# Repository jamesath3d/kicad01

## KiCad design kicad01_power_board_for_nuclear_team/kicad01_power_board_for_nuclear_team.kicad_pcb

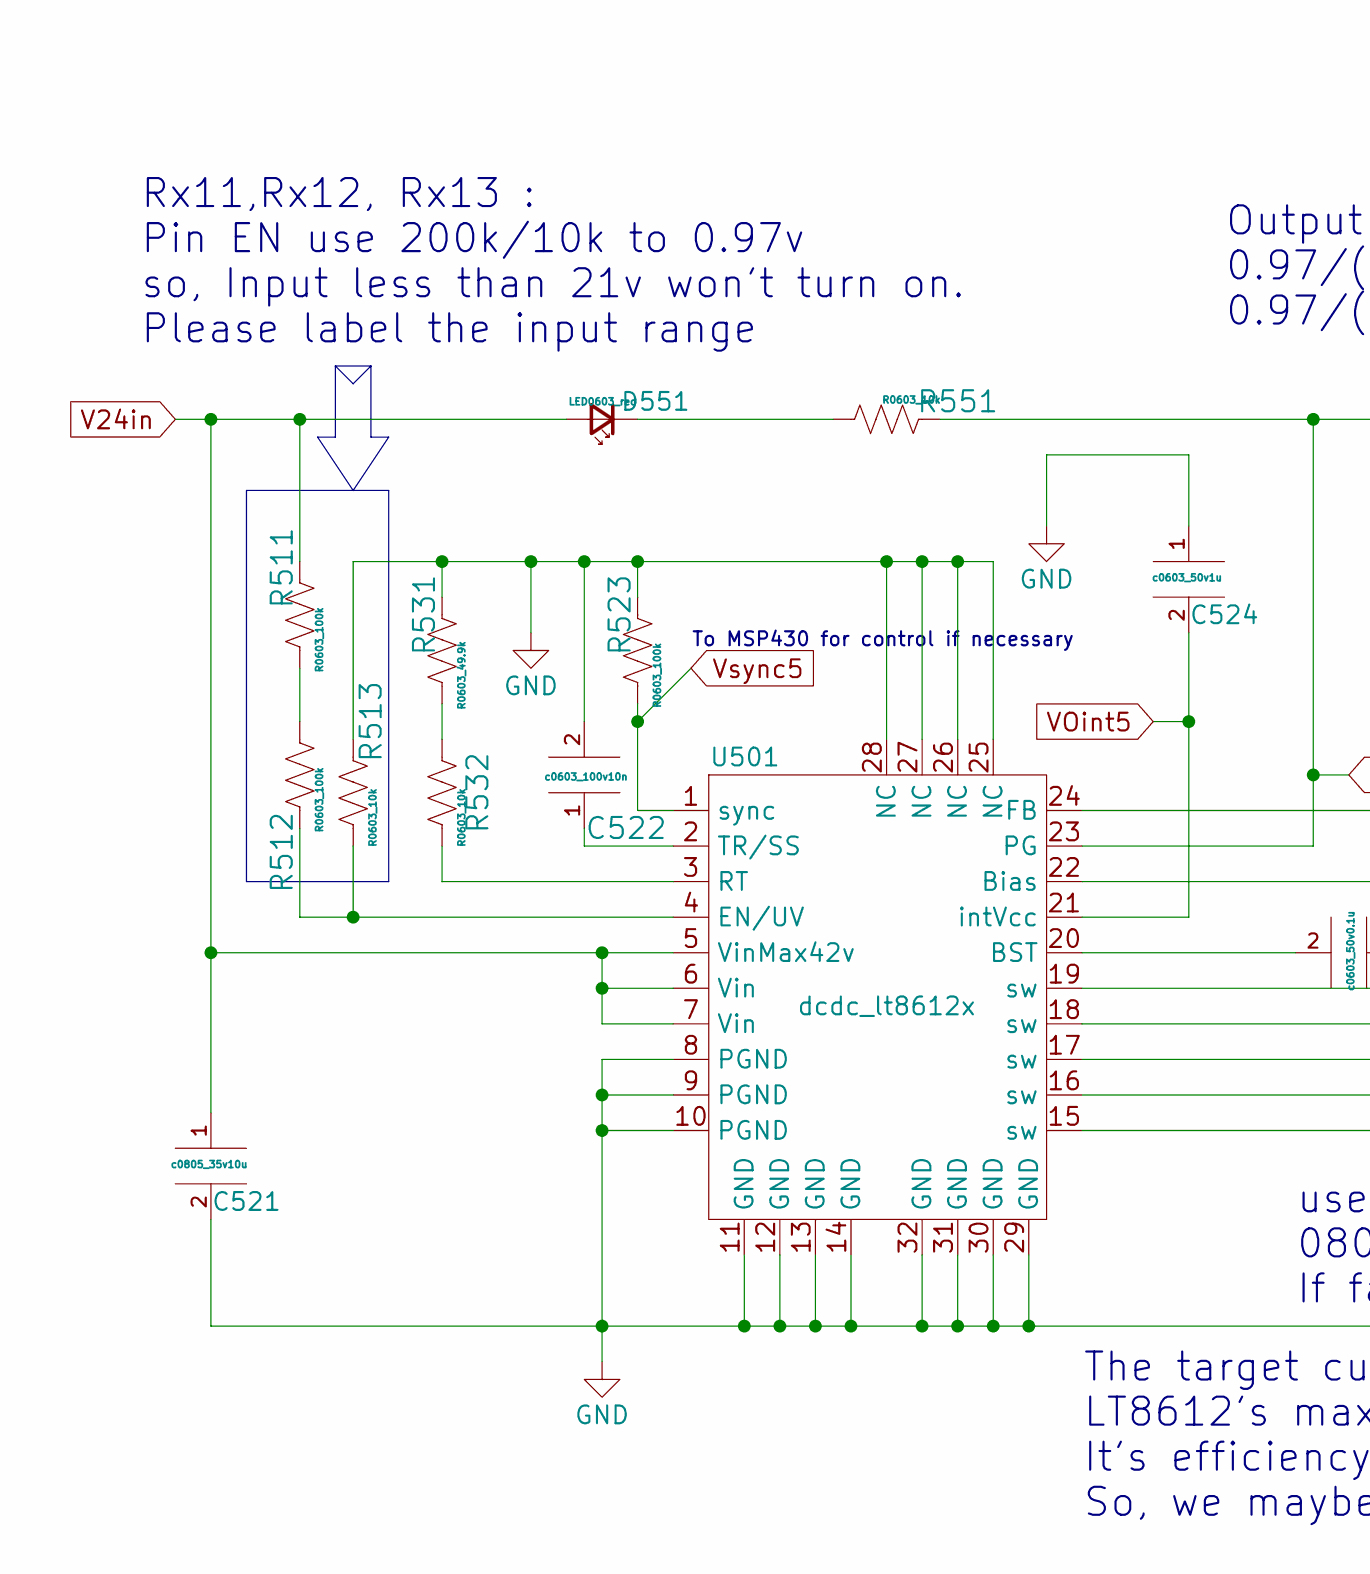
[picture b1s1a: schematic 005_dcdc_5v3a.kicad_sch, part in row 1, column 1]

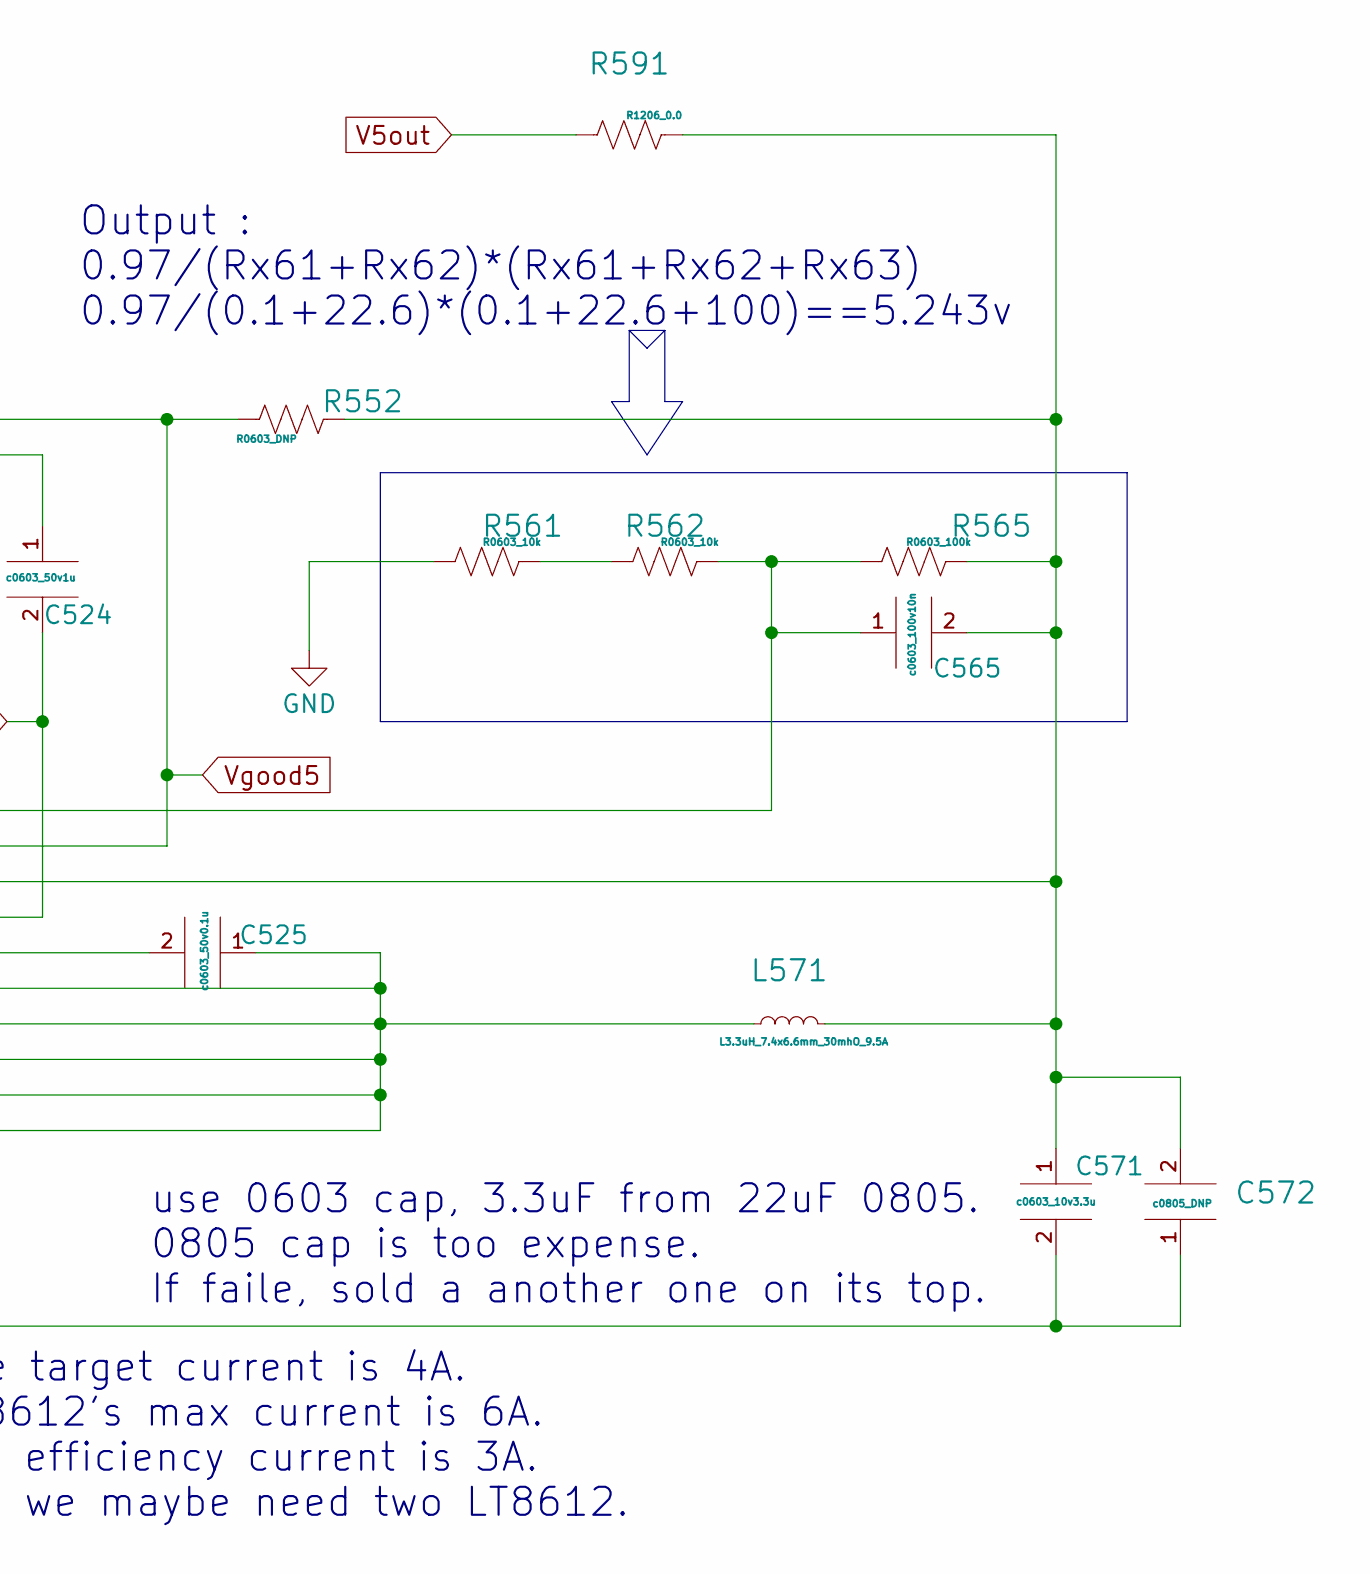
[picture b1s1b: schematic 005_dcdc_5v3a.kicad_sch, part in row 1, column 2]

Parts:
C521: c0805_35v10u; C0805mix0603; PartNum C2012X5R1V106M085AC
C522, C565: c0603_100v10n; C0603; PartNum C1608X7R2A103M080AA
C524: c0603_50v1u; C0603; PartNum C1608X5R1H105K080AB
C525: c0603_50v0.1u; C0603; PartNum CGA3E2X7R1H104M080AA
C571: c0603_10v3.3u; C0603; PartNum C1608X7S1A335K080AC
C572: c0805_DNP; C0805mix0603; PartNum c0805_DNP
D551: LED0603_red; LED0603; PartNum LTST-C190KRKT
L571: L3.3uH_7.4x6.6mm_30mhO_9.5A; L7.1x6.6mm; PartNum ECS-MPIL0630-3R3MC
R511, R512, R523, R565: R0603_100k; C0603; PartNum ERA-3AED104V
R513, R532, R551, R561, R562: R0603_10k; C0603; PartNum ERJ-PA3F1002V
R531: R0603_49.9k; C0603; PartNum ERA-3AED4992V
R552: R0603_DNP; C0603; PartNum R0603_DNP
R591: R1206_0.0; R1206mix0603; PartNum RC1206FR-070RL
U501: dcdc_lt8612x; QFN-28-1EP_3x6mm_P0.5mm_EP1.7x4.75mmX; PartNum 505-LT8612EUDE#PBF-ND

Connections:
GND: C521.2, C522.2, C524.1, C571.2, C572.1, R513.2, R523.2, R531.2, R561.2, U501.8 (PGND), U501.9 (PGND), U501.10 (PGND), U501.11 (GND), U501.12 (GND), U501.13 (GND), U501.14 (GND), U501.25 (NC), U501.26 (NC), U501.27 (NC), U501.28 (NC), U501.29 (GND), U501.30 (GND), U501.31 (GND), U501.32 (GND); also elsewhere on the board
unnamed: C522.1, U501.2 (TR/SS)
unnamed: C525.1, L571.1, U501.15 (sw), U501.16 (sw), U501.17 (sw), U501.18 (sw), U501.19 (sw)
unnamed: C525.2, U501.20 (BST)
unnamed: C565.1, R562.1, R565.2, U501.24 (FB)
unnamed: C565.2, C571.1, C572.2, L571.2, R552.2, R565.1, R591.1, U501.22 (Bias)
unnamed: D551.1 (K), R551.2
unnamed: R511.1, R512.2
unnamed: R512.1, R513.1, U501.4 (EN/UV)
unnamed: R531.1, R532.2
unnamed: R532.1, U501.3 (RT)
unnamed: R561.1, R562.2
V5out: R591.2; also elsewhere on the board
V24in: C521.1, D551.2 (A), R511.2, U501.5 (VinMax42v), U501.6 (Vin), U501.7 (Vin); also elsewhere on the board
VOint5: C524.2, U501.21 (intVcc)
Vgood5: R551.1, R552.1, U501.23 (PG)
Vsync5: R523.1, U501.1 (sync)

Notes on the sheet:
use 0603 cap, 3.3uF from 22uF 0805. 0805 cap is too expense. If faile, sold a another one on its top.
To MSP430 for control if necessary
The target current is 4A. LT8612's max current is 6A. It's efficiency current is 3A. So, we maybe need two LT8612.
Output : 0.97/(Rx61+Rx62)*(Rx61+Rx62+Rx63) 0.97/(0.1+22.6)*(0.1+22.6+100)==5.243v
Rx11,Rx12, Rx13 : Pin EN use 200k/10k to 0.97v so, Input less than 21v won't turn on. Please label the input range

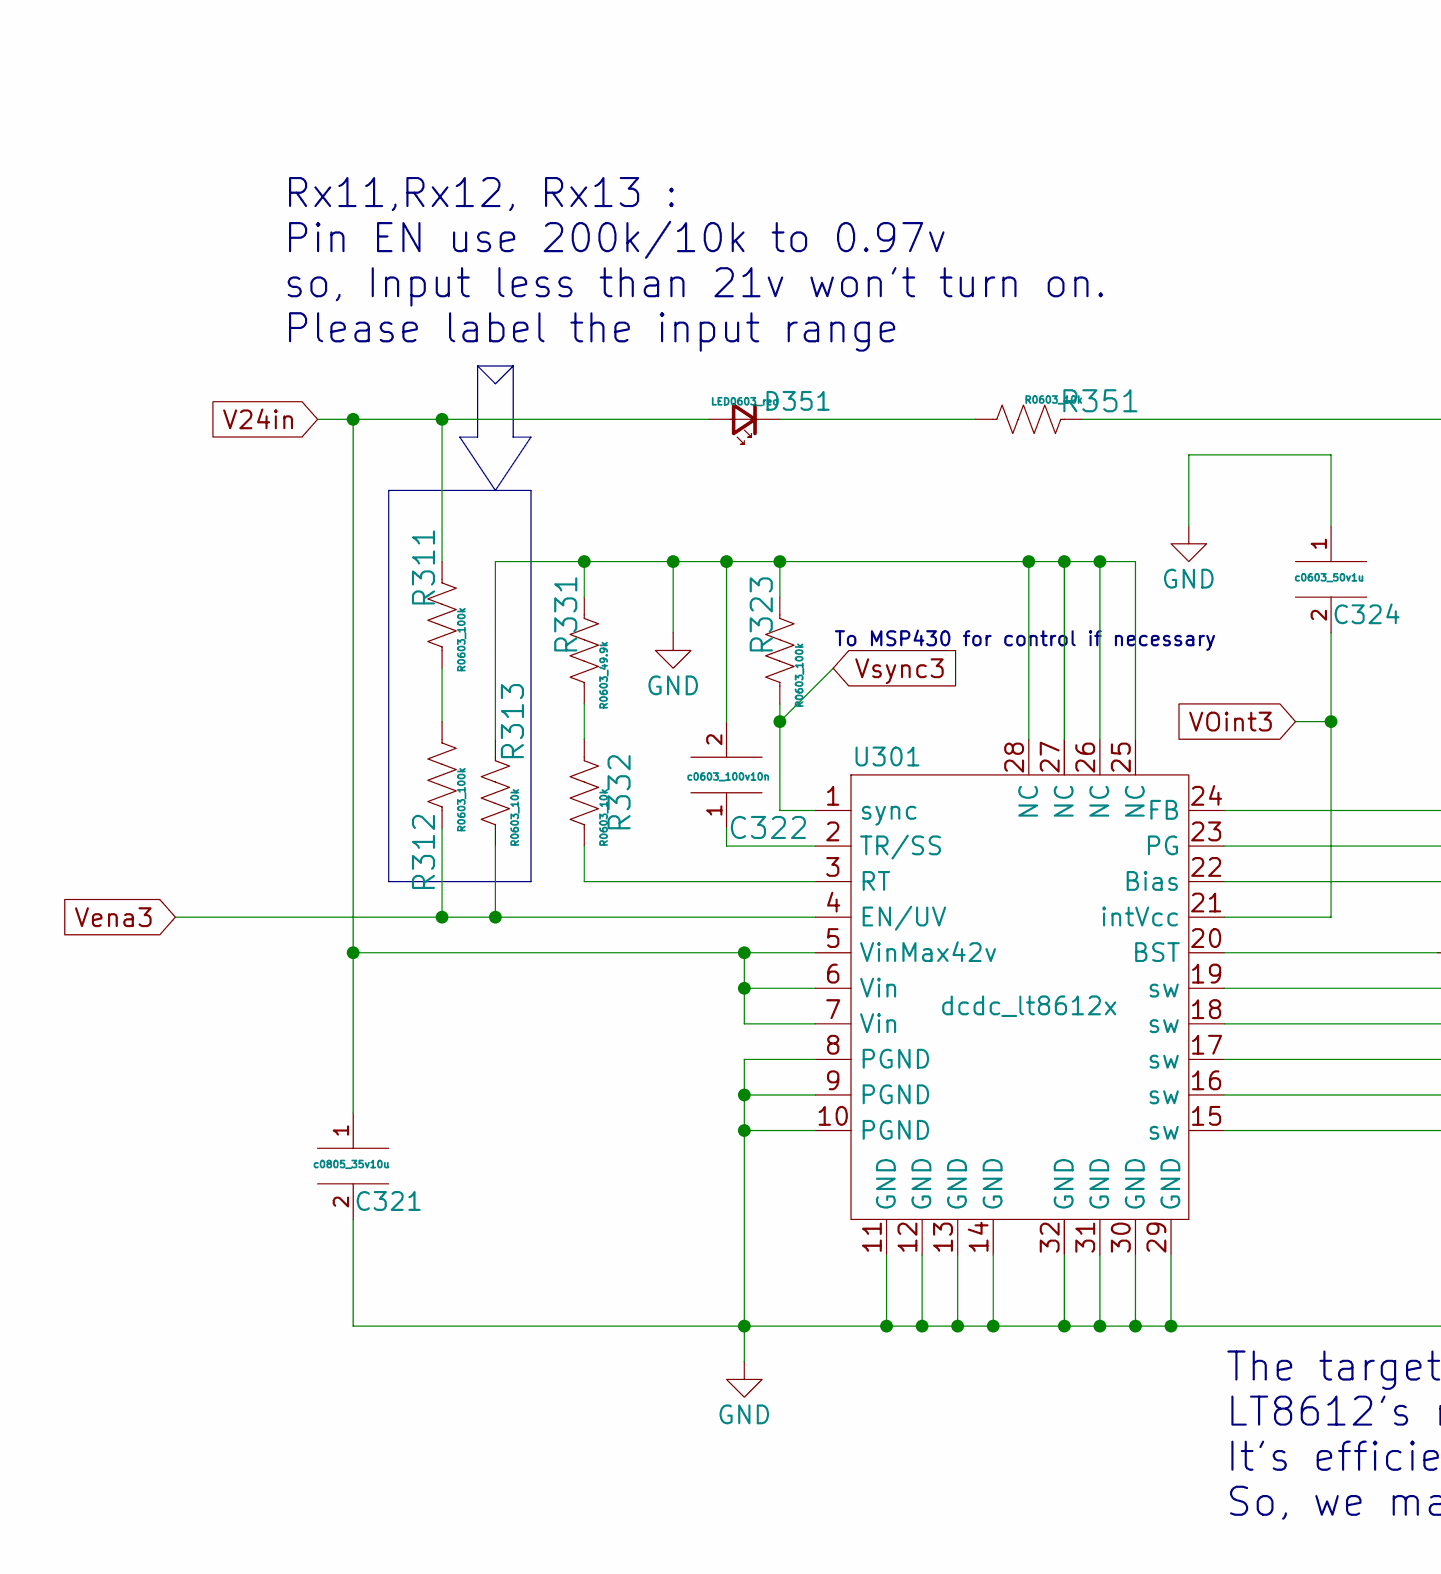
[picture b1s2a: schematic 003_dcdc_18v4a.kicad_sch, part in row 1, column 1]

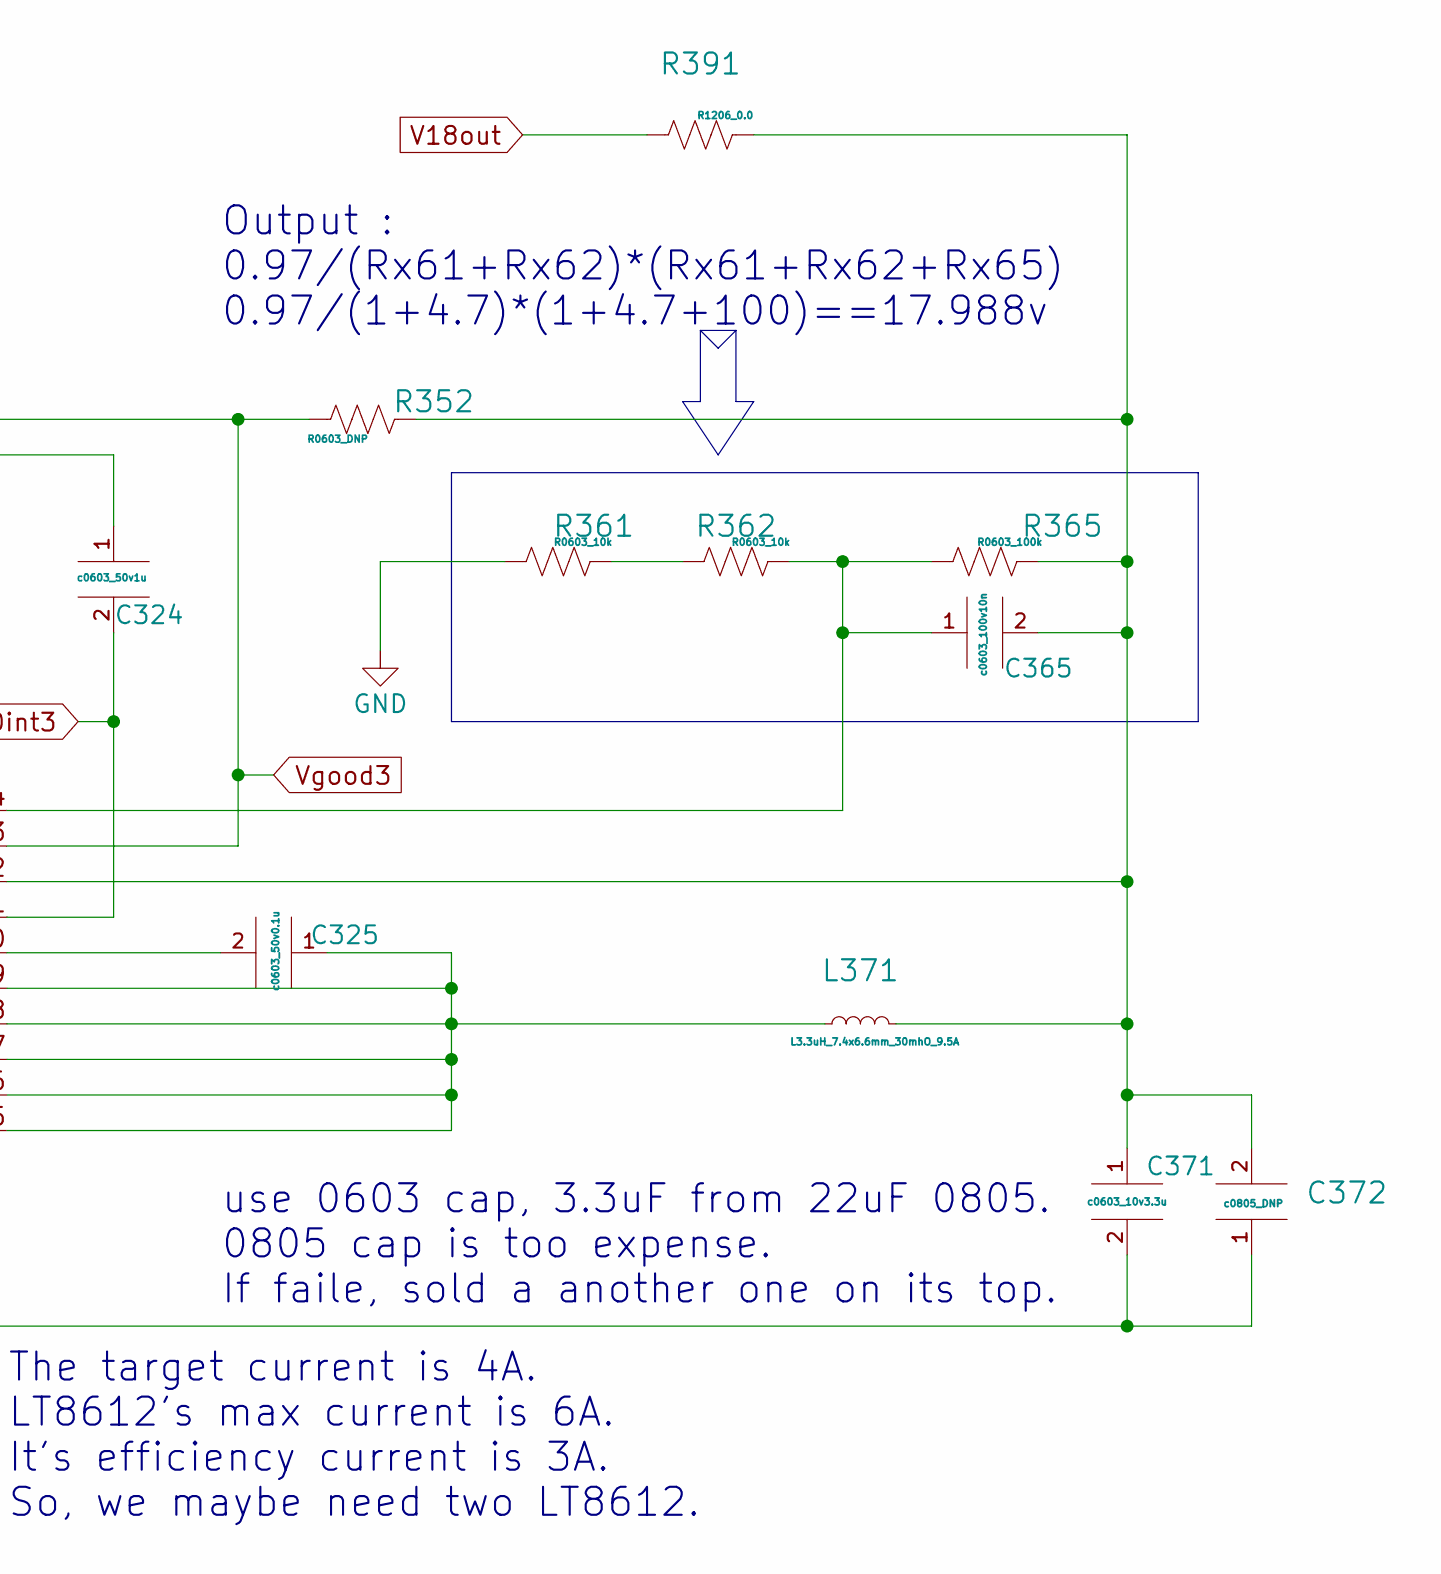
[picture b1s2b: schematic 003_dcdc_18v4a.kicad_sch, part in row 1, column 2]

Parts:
C321: c0805_35v10u; C0805mix0603; PartNum C2012X5R1V106M085AC
C322, C365: c0603_100v10n; C0603; PartNum C1608X7R2A103M080AA
C324: c0603_50v1u; C0603; PartNum C1608X5R1H105K080AB
C325: c0603_50v0.1u; C0603; PartNum CGA3E2X7R1H104M080AA
C371: c0603_10v3.3u; C0603; PartNum C1608X7S1A335K080AC
C372: c0805_DNP; C0805mix0603; PartNum c0805_DNP
D351: LED0603_red; LED0603; PartNum LTST-C190KRKT
L371: L3.3uH_7.4x6.6mm_30mhO_9.5A; L7.1x6.6mm; PartNum ECS-MPIL0630-3R3MC
R311, R312, R323, R365: R0603_100k; R0603; PartNum ERA-3AED104V
R313, R332, R351, R361, R362: R0603_10k; R0603; PartNum ERJ-PA3F1002V
R331: R0603_49.9k; R0603; PartNum ERA-3AED4992V
R352: R0603_DNP; R0603; PartNum R0603_DNP
R391: R1206_0.0; R1206mix0603; PartNum RC1206FR-070RL
U301: dcdc_lt8612x; QFN-28-1EP_3x6mm_P0.5mm_EP1.7x4.75mmX; PartNum 505-LT8612EUDE#PBF-ND

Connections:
GND: C321.2, C322.2, C324.1, C371.2, C372.1, R313.2, R323.2, R331.2, R361.2, U301.8 (PGND), U301.9 (PGND), U301.10 (PGND), U301.11 (GND), U301.12 (GND), U301.13 (GND), U301.14 (GND), U301.25 (NC), U301.26 (NC), U301.27 (NC), U301.28 (NC), U301.29 (GND), U301.30 (GND), U301.31 (GND), U301.32 (GND); also elsewhere on the board
unnamed: C322.1, U301.2 (TR/SS)
unnamed: C325.1, L371.1, U301.15 (sw), U301.16 (sw), U301.17 (sw), U301.18 (sw), U301.19 (sw)
unnamed: C325.2, U301.20 (BST)
unnamed: C365.1, R362.1, R365.2, U301.24 (FB)
unnamed: C365.2, C371.1, C372.2, L371.2, R352.2, R365.1, R391.1, U301.22 (Bias)
unnamed: D351.1 (K), R351.2
unnamed: R311.1, R312.2
unnamed: R331.1, R332.2
unnamed: R332.1, U301.3 (RT)
unnamed: R361.1, R362.2
V18out: R391.2; also elsewhere on the board
V24in: C321.1, D351.2 (A), R311.2, U301.5 (VinMax42v), U301.6 (Vin), U301.7 (Vin); also elsewhere on the board
VOint3: C324.2, U301.21 (intVcc); also elsewhere on the board
Vena3: R312.1, R313.1, U301.4 (EN/UV); also elsewhere on the board
Vgood3: R351.1, R352.1, U301.23 (PG); also elsewhere on the board
Vsync3: R323.1, U301.1 (sync); also elsewhere on the board

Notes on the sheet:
To MSP430 for control if necessary
use 0603 cap, 3.3uF from 22uF 0805. 0805 cap is too expense. If faile, sold a another one on its top.
Output : 0.97/(Rx61+Rx62)*(Rx61+Rx62+Rx65) 0.97/(1+4.7)*(1+4.7+100)==17.988v
Rx11,Rx12, Rx13 : Pin EN use 200k/10k to 0.97v so, Input less than 21v won't turn on. Please label the input range
The target current is 4A. LT8612's max current is 6A. It's efficiency current is 3A. So, we maybe need two LT8612.

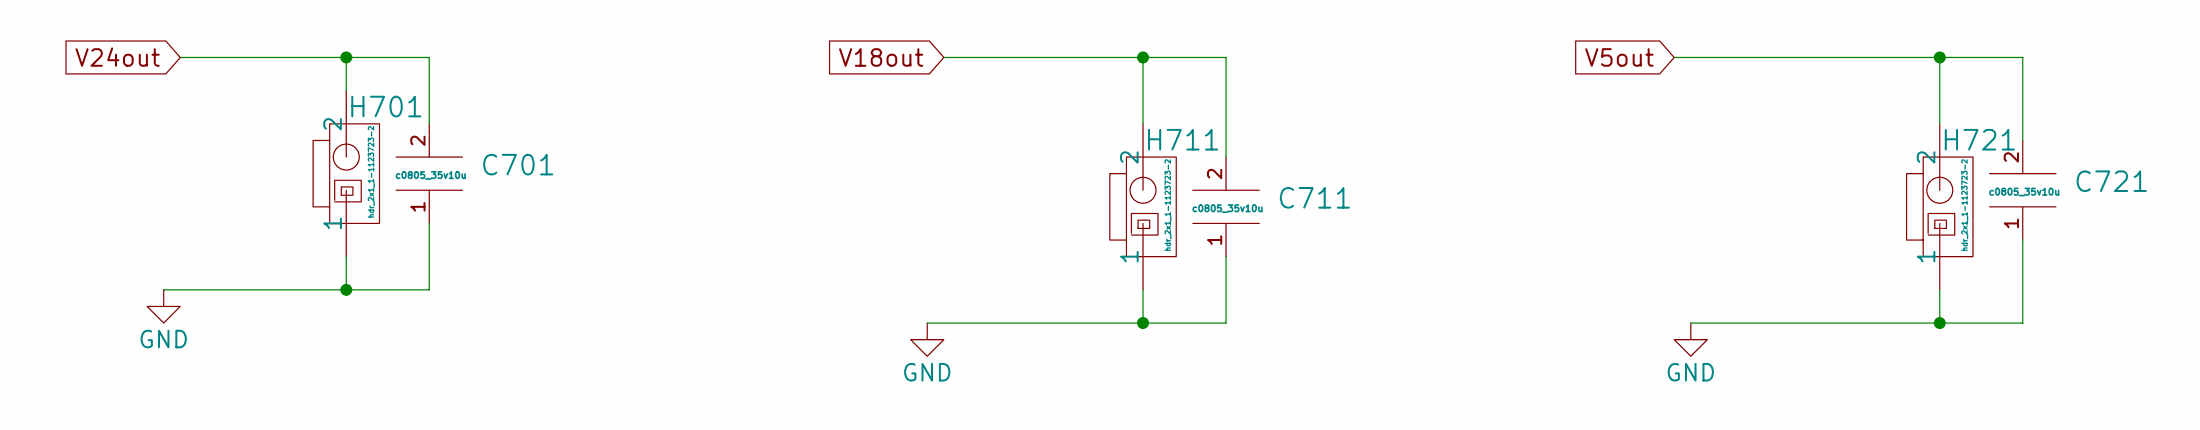
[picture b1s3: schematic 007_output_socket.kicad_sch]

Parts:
C701, C711, C721: c0805_35v10u; C0805mix0603; PartNum C2012X5R1V106M085AC
H701, H711, H721: hdr_2x1_1-1123723-2; PartNum 1-1123723-2

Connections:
GND: C701.1, C711.1, C721.1, H701.1, H711.1, H721.1; also elsewhere on the board
V5out: C721.2, H721.2; also elsewhere on the board
V18out: C711.2, H711.2; also elsewhere on the board
V24out: C701.2, H701.2; also elsewhere on the board

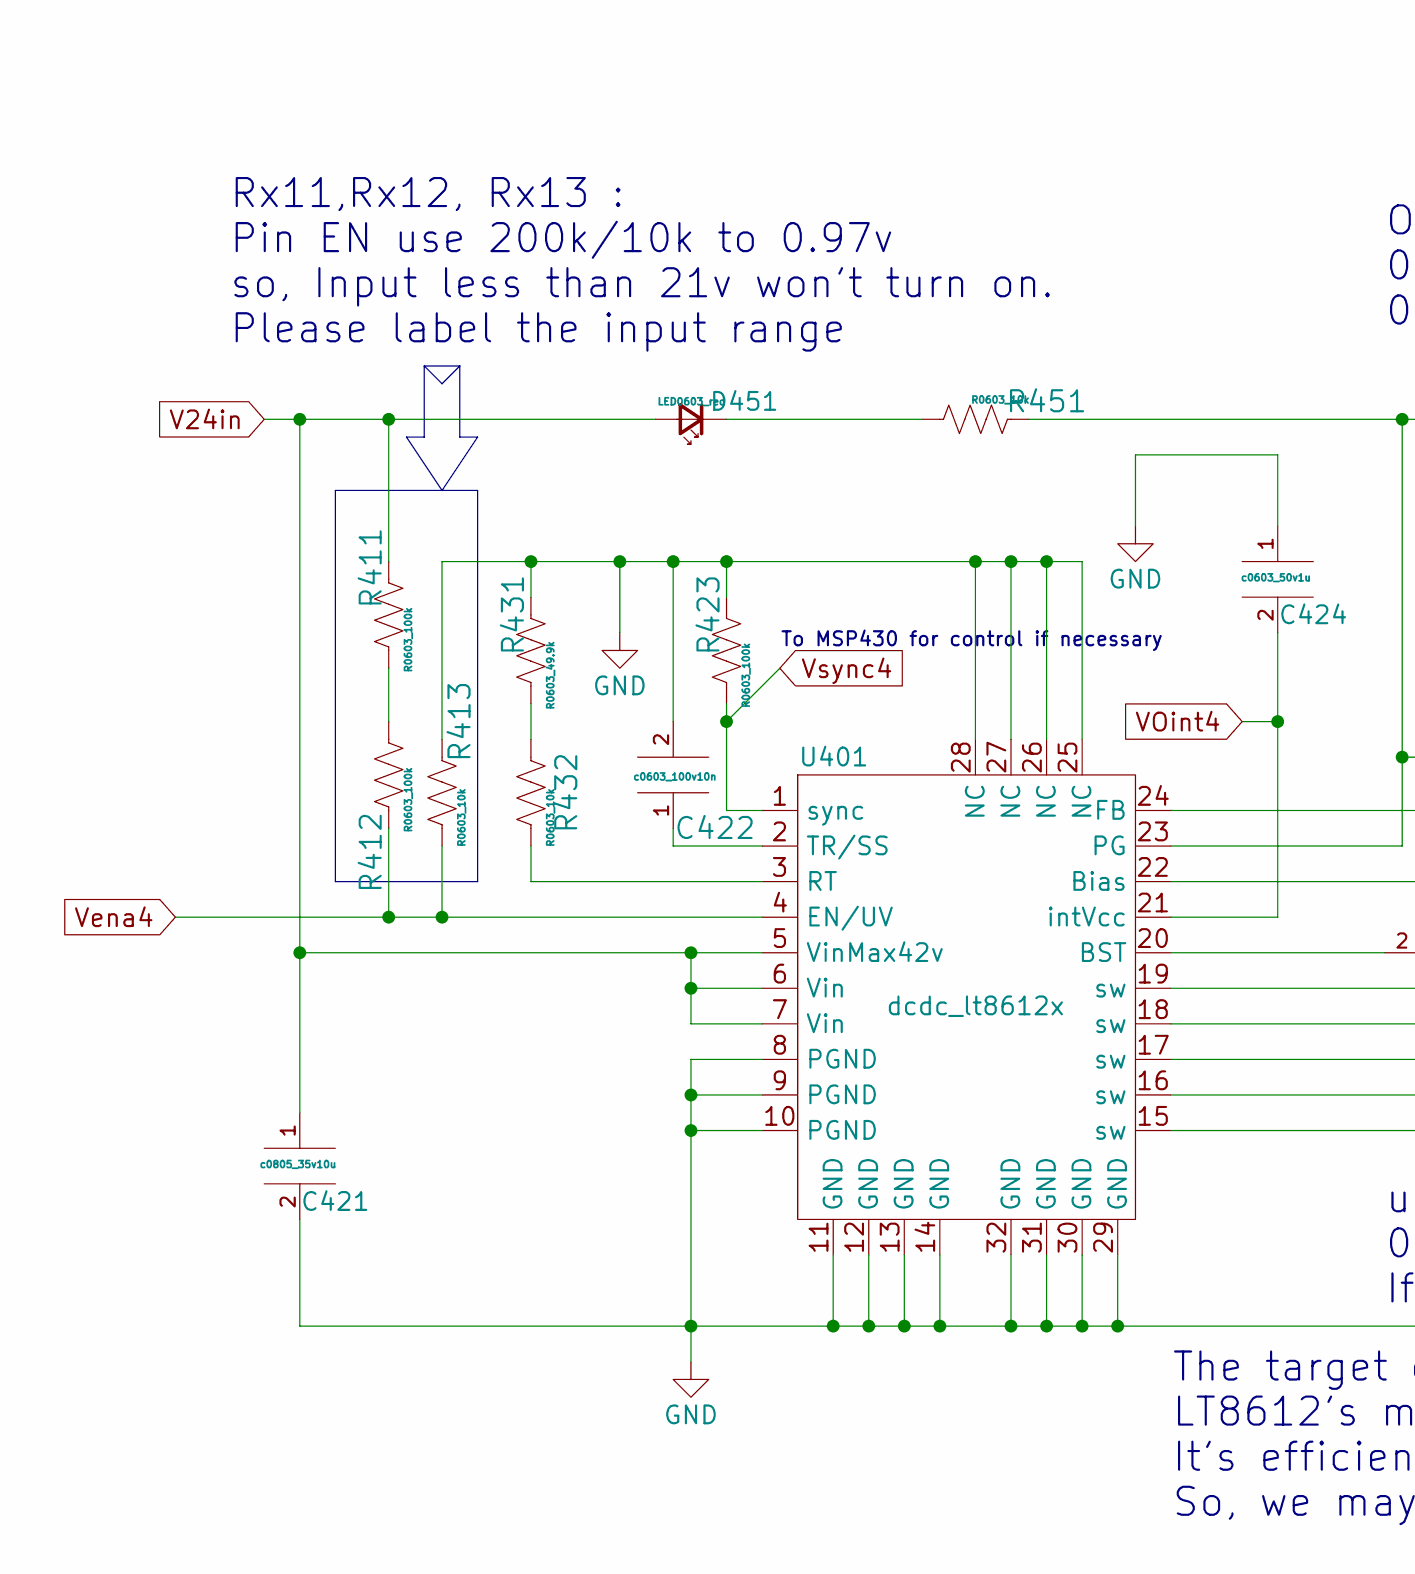
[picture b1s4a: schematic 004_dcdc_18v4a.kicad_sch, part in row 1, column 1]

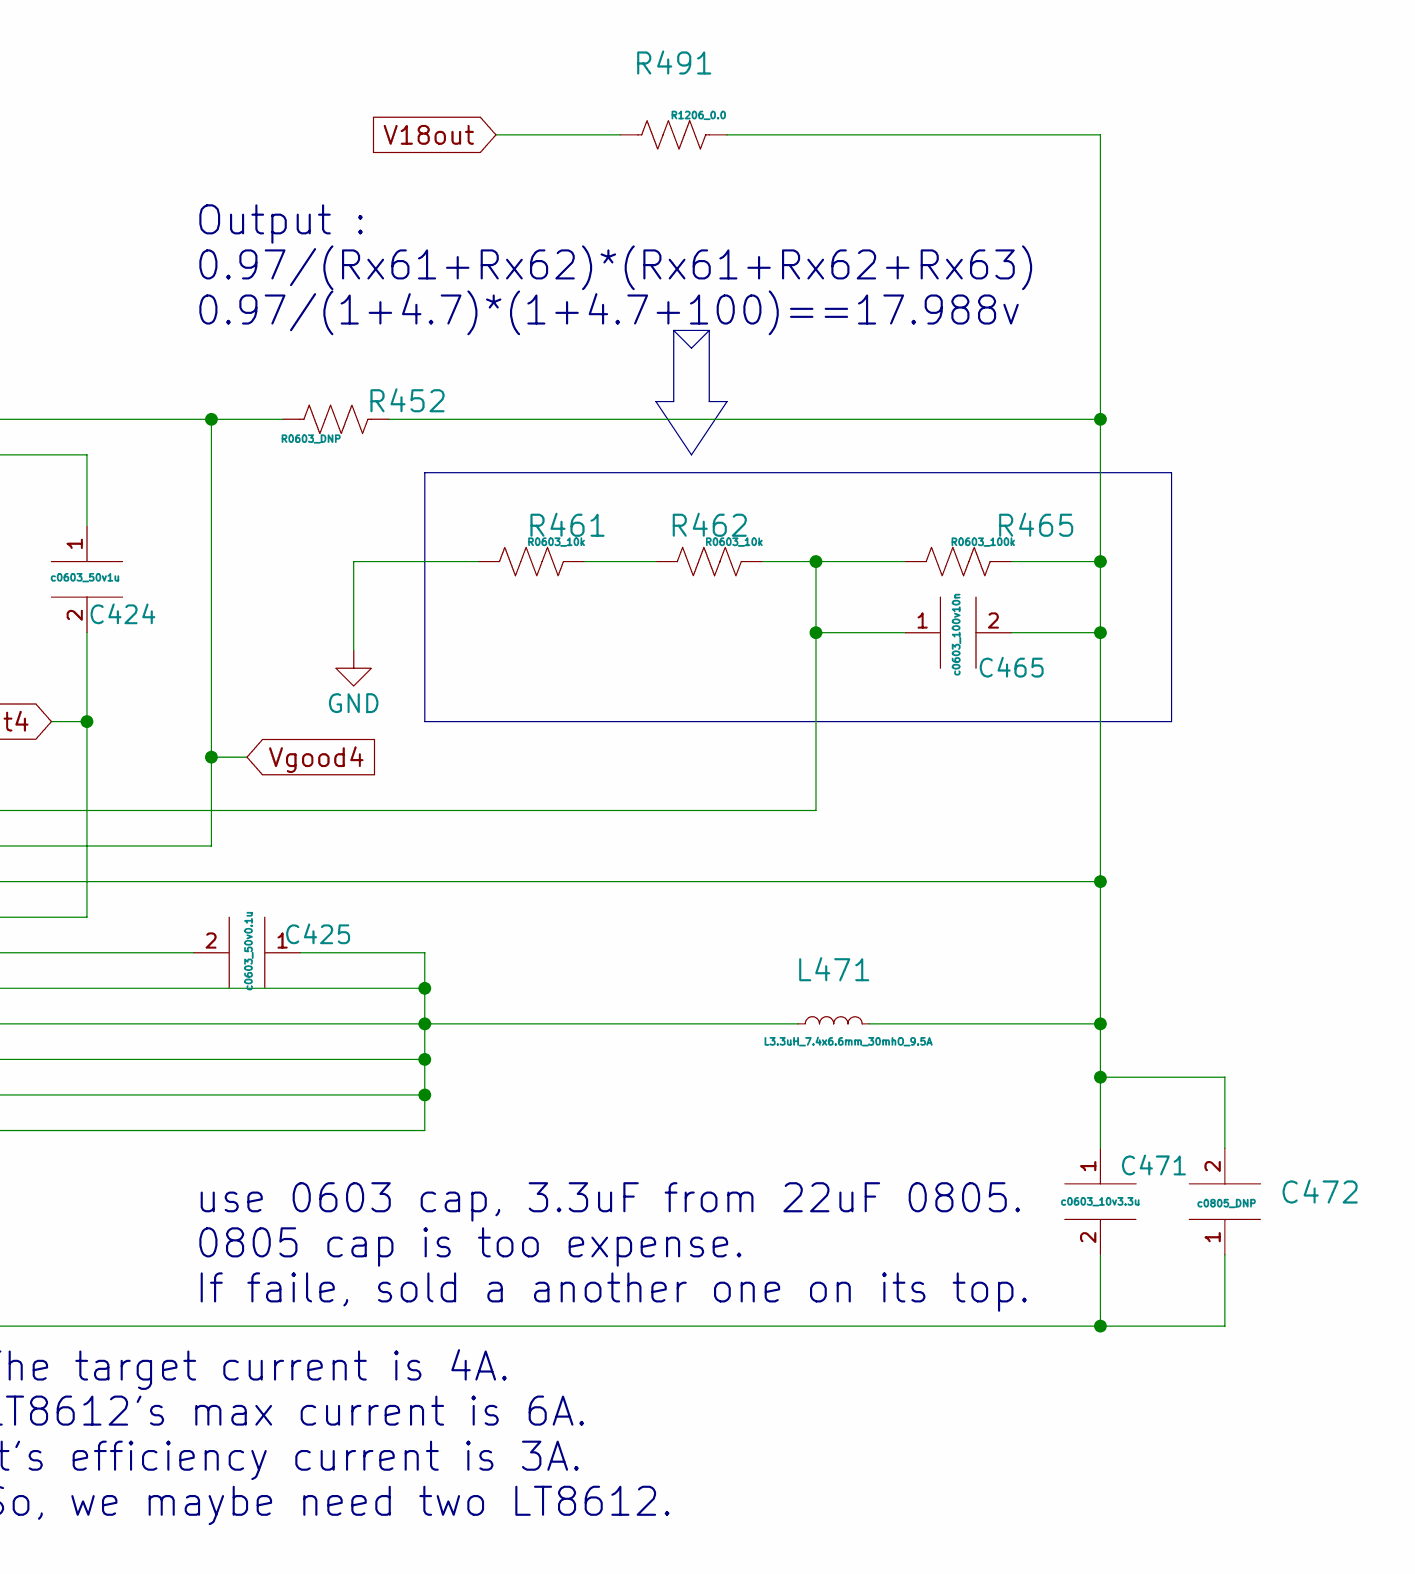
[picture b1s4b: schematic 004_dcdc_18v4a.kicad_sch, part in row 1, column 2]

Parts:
C421: c0805_35v10u; C0805mix0603; PartNum C2012X5R1V106M085AC
C422, C465: c0603_100v10n; C0603; PartNum C1608X7R2A103M080AA
C424: c0603_50v1u; C0603; PartNum C1608X5R1H105K080AB
C425: c0603_50v0.1u; C0603; PartNum CGA3E2X7R1H104M080AA
C471: c0603_10v3.3u; C0603; PartNum C1608X7S1A335K080AC
C472: c0805_DNP; C0805mix0603; PartNum c0805_DNP
D451: LED0603_red; LED0603; PartNum LTST-C190KRKT
L471: L3.3uH_7.4x6.6mm_30mhO_9.5A; L7.1x6.6mm; PartNum ECS-MPIL0630-3R3MC
R411, R412, R423, R465: R0603_100k; R0603; PartNum ERA-3AED104V
R413, R432, R451, R461, R462: R0603_10k; R0603; PartNum ERJ-PA3F1002V
R431: R0603_49.9k; R0603; PartNum ERA-3AED4992V
R452: R0603_DNP; R0603; PartNum R0603_DNP
R491: R1206_0.0; R1206mix0603; PartNum RC1206FR-070RL
U401: dcdc_lt8612x; QFN-28-1EP_3x6mm_P0.5mm_EP1.7x4.75mmX; PartNum 505-LT8612EUDE#PBF-ND

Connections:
GND: C421.2, C422.2, C424.1, C471.2, C472.1, R413.2, R423.2, R431.2, R461.2, U401.8 (PGND), U401.9 (PGND), U401.10 (PGND), U401.11 (GND), U401.12 (GND), U401.13 (GND), U401.14 (GND), U401.25 (NC), U401.26 (NC), U401.27 (NC), U401.28 (NC), U401.29 (GND), U401.30 (GND), U401.31 (GND), U401.32 (GND); also elsewhere on the board
unnamed: C422.1, U401.2 (TR/SS)
unnamed: C425.1, L471.1, U401.15 (sw), U401.16 (sw), U401.17 (sw), U401.18 (sw), U401.19 (sw)
unnamed: C425.2, U401.20 (BST)
unnamed: C465.1, R462.1, R465.2, U401.24 (FB)
unnamed: C465.2, C471.1, C472.2, L471.2, R452.2, R465.1, R491.1, U401.22 (Bias)
unnamed: D451.1 (K), R451.2
unnamed: R411.1, R412.2
unnamed: R431.1, R432.2
unnamed: R432.1, U401.3 (RT)
unnamed: R461.1, R462.2
V18out: R491.2; also elsewhere on the board
V24in: C421.1, D451.2 (A), R411.2, U401.5 (VinMax42v), U401.6 (Vin), U401.7 (Vin); also elsewhere on the board
VOint4: C424.2, U401.21 (intVcc); also elsewhere on the board
Vena4: R412.1, R413.1, U401.4 (EN/UV); also elsewhere on the board
Vgood4: R451.1, R452.1, U401.23 (PG); also elsewhere on the board
Vsync4: R423.1, U401.1 (sync); also elsewhere on the board

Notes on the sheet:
Output : 0.97/(Rx61+Rx62)*(Rx61+Rx62+Rx63) 0.97/(1+4.7)*(1+4.7+100)==17.988v
Rx11,Rx12, Rx13 : Pin EN use 200k/10k to 0.97v so, Input less than 21v won't turn on. Please label the input range
use 0603 cap, 3.3uF from 22uF 0805. 0805 cap is too expense. If faile, sold a another one on its top.
The target current is 4A. LT8612's max current is 6A. It's efficiency current is 3A. So, we maybe need two LT8612.
To MSP430 for control if necessary
